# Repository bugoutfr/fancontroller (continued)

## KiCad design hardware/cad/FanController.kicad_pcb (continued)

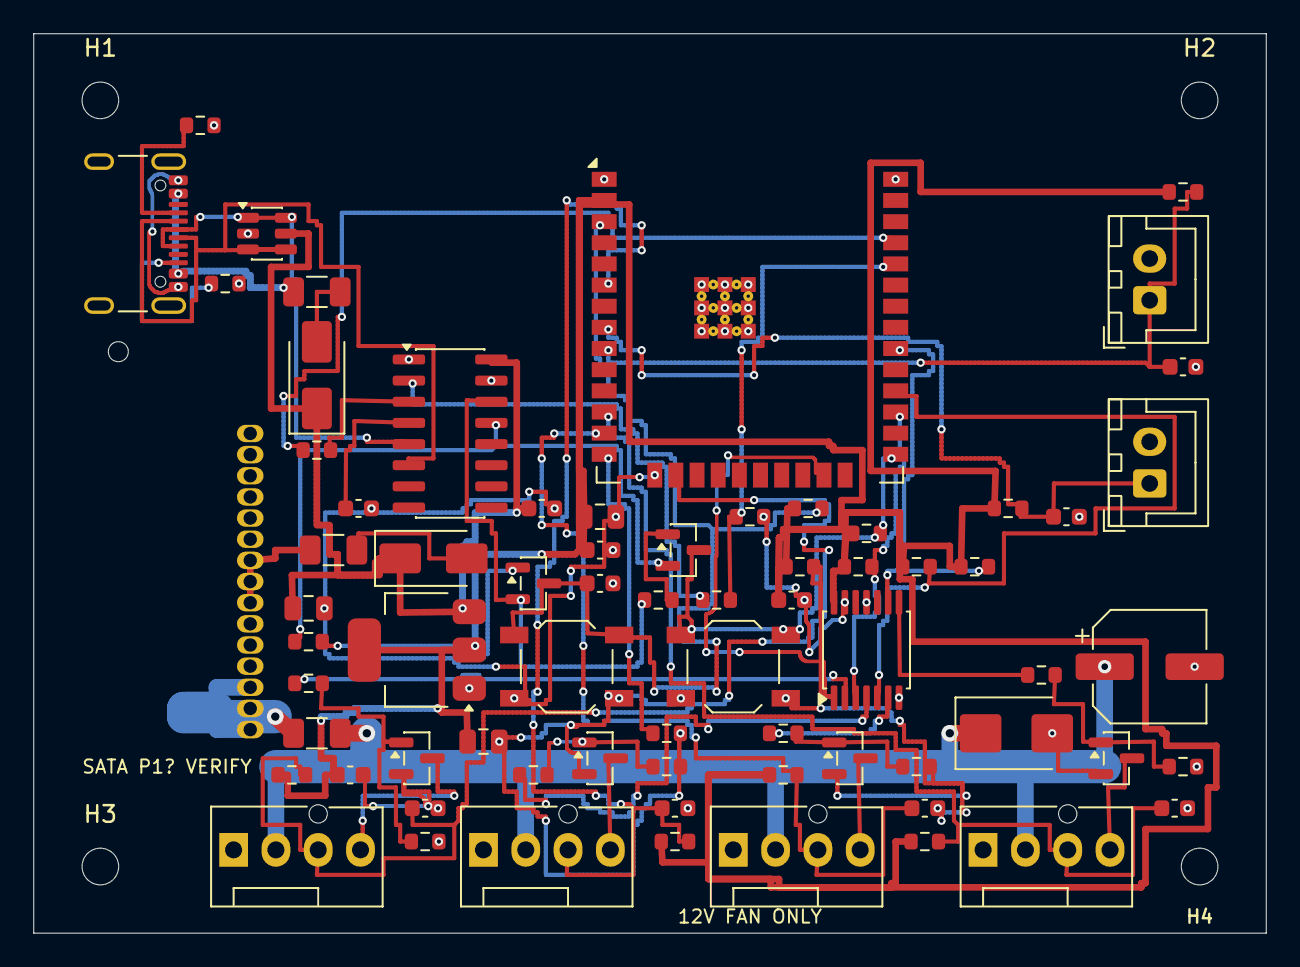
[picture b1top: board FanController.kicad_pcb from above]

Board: 2 copper layers, 74.0 x 54.0 mm, 75 parts (0 on the bottom side), 47 nets.

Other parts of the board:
H1, H2, H3, H4: M2_NPTH_2.2mm; MountingHole_2.2mm_M2

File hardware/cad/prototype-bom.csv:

ref,value,footprint,source
J1,SATA_POWER_B_PROVISIONAL,FanController:SATA_Power_B_Provisional,https://ae-pic-a1.aliexpress-media.com/kf/S0ac0b9d23cc148d9b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
J2,GCT_USB4105-GF-A,Connector_USB:USB_C_Receptacle_GCT_USB4105-xx-A_16P_TopMnt_Horizontal,https://gct.co/files/drawings/usb4105.pdf
F1,3.15A_T_1206_VERIFY_I2T,Fuse:Fuse_1206_3216Metric,
F2,1A_PTC_1206,Fuse:Fuse_1206_3216Metric,
F3,0.5A_PTC_1206,Fuse:Fuse_1206_3216Metric,
D1,SS14,Diode_SMD:D_SMA,https://www.vishay.com/docs/88746/ss12.pdf
D2,SS14,Diode_SMD:D_SMA,https://www.vishay.com/docs/88746/ss12.pdf
D3,SMBJ15A_TVS,Diode_SMD:D_SMB,https://www.vishay.com/docs/88392/smbj.pdf
U2,TLV1117LV33DCYR,Package_TO_SOT_SMD:SOT-223-3_TabPin2,https://www.ti.com/lit/ds/symlink/tlv1117lv.pdf
C1,100uF_25V,Capacitor_SMD:CP_Elec_6.3x7.7,
C2,10uF_10V_X7R,Capacitor_SMD:C_0805_2012Metric,
C3,22uF_6.3V_X5R,Capacitor_SMD:C_0805_2012Metric,
C4,100nF_16V,Capacitor_SMD:C_0603_1608Metric,
C5,100nF_16V,Capacitor_SMD:C_0603_1608Metric,
C6,100nF_16V,Capacitor_SMD:C_0603_1608Metric,
U3,CH340C,Package_SO:SOIC-16_3.9x9.9mm_P1.27mm,https://www.wch-ic.com/downloads/CH340DS1_PDF.html
U4,USBLC6-2SC6,Package_TO_SOT_SMD:SOT-23-6,https://www.st.com/resource/en/datasheet/usblc6-2.pdf
R1,5.1k_1%,Resistor_SMD:R_0603_1608Metric,
R2,5.1k_1%,Resistor_SMD:R_0603_1608Metric,
R3,1k_1%,Resistor_SMD:R_0603_1608Metric,
R4,2k_1%,Resistor_SMD:R_0603_1608Metric,
R5,1k,Resistor_SMD:R_0603_1608Metric,
U1,ESP32-WROOM-32E-N4,RF_Module:ESP32-WROOM-32E,https://documentation.espressif.com/esp32-wroom-32e_esp32-wr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
C7,22uF_6.3V_X5R,Capacitor_SMD:C_0805_2012Metric,
C8,100nF_16V,Capacitor_SMD:C_0603_1608Metric,
R6,10k,Resistor_SMD:R_0603_1608Metric,
C9,1uF_10V_X7R,Capacitor_SMD:C_0603_1608Metric,
R7,10k,Resistor_SMD:R_0603_1608Metric,
R8,10k,Resistor_SMD:R_0603_1608Metric,
SW1,RESET,Button_Switch_SMD:SW_SPST_TL3342,
SW2,BOOT,Button_Switch_SMD:SW_SPST_TL3342,
Q5,MMBT3904LT1G,Package_TO_SOT_SMD:SOT-23,https://www.onsemi.com/pdf/datasheet/mmbt3904lt1-d.pdf
Q6,MMBT3904LT1G,Package_TO_SOT_SMD:SOT-23,https://www.onsemi.com/pdf/datasheet/mmbt3904lt1-d.pdf
R9,10k,Resistor_SMD:R_0603_1608Metric,
R10,10k,Resistor_SMD:R_0603_1608Metric,
U5,SN74LVC14APWR,Package_SO:TSSOP-14_4.4x5mm_P0.65mm,https://www.ti.com/lit/ds/symlink/sn74lvc14a.pdf
C10,100nF_16V,Capacitor_SMD:C_0603_1608Metric,
J3,FAN1_Molex_47053-1000,Connector:FanPinHeader_1x04_P2.54mm_Vertical,https://www.molex.com/en-us/products/part-detail/470531000
Q1,MMBT3904LT1G,Package_TO_SOT_SMD:SOT-23,https://www.onsemi.com/pdf/datasheet/mmbt3904lt1-d.pdf
R11,10k,Resistor_SMD:R_0603_1608Metric,
R15,2.2k,Resistor_SMD:R_0603_1608Metric,
R19,100k,Resistor_SMD:R_0603_1608Metric,
R23,5.23k_1%,Resistor_SMD:R_0603_1608Metric,
C11,100pF_C0G,Capacitor_SMD:C_0603_1608Metric,
J4,FAN2_Molex_47053-1000,Connector:FanPinHeader_1x04_P2.54mm_Vertical,https://www.molex.com/en-us/products/part-detail/470531000
Q2,MMBT3904LT1G,Package_TO_SOT_SMD:SOT-23,https://www.onsemi.com/pdf/datasheet/mmbt3904lt1-d.pdf
R12,10k,Resistor_SMD:R_0603_1608Metric,
R16,2.2k,Resistor_SMD:R_0603_1608Metric,
R20,100k,Resistor_SMD:R_0603_1608Metric,
R24,5.23k_1%,Resistor_SMD:R_0603_1608Metric,
C12,100pF_C0G,Capacitor_SMD:C_0603_1608Metric,
J5,FAN3_Molex_47053-1000,Connector:FanPinHeader_1x04_P2.54mm_Vertical,https://www.molex.com/en-us/products/part-detail/470531000
Q3,MMBT3904LT1G,Package_TO_SOT_SMD:SOT-23,https://www.onsemi.com/pdf/datasheet/mmbt3904lt1-d.pdf
R13,10k,Resistor_SMD:R_0603_1608Metric,
R17,2.2k,Resistor_SMD:R_0603_1608Metric,
R21,100k,Resistor_SMD:R_0603_1608Metric,
R25,5.23k_1%,Resistor_SMD:R_0603_1608Metric,
C13,100pF_C0G,Capacitor_SMD:C_0603_1608Metric,
J6,FAN4_Molex_47053-1000,Connector:FanPinHeader_1x04_P2.54mm_Vertical,https://www.molex.com/en-us/products/part-detail/470531000
Q4,MMBT3904LT1G,Package_TO_SOT_SMD:SOT-23,https://www.onsemi.com/pdf/datasheet/mmbt3904lt1-d.pdf
R14,10k,Resistor_SMD:R_0603_1608Metric,
R18,2.2k,Resistor_SMD:R_0603_1608Metric,
R22,100k,Resistor_SMD:R_0603_1608Metric,
R26,5.23k_1%,Resistor_SMD:R_0603_1608Metric,
C14,100pF_C0G,Capacitor_SMD:C_0603_1608Metric,
J7,NTC1_10k_B3950,Connector_JST:JST_XH_B2B-XH-A_1x02_P2.50mm_Vertical,https://www.jst-mfg.com/product/pdf/eng/eXH.pdf
R27,10k_1%,Resistor_SMD:R_0603_1608Metric,
C15,100nF_16V,Capacitor_SMD:C_0603_1608Metric,
J8,NTC2_10k_B3950,Connector_JST:JST_XH_B2B-XH-A_1x02_P2.50mm_Vertical,https://www.jst-mfg.com/product/pdf/eng/eXH.pdf
R28,10k_1%,Resistor_SMD:R_0603_1608Metric,
C16,100nF_16V,Capacitor_SMD:C_0603_1608Metric,

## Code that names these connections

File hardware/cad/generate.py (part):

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    esp_nets = {i: None for i in range(1, 40)}
    esp_nets.update({1: "GND", 2: "+3V3", 3: "ESP_EN", 6: "FAN2_TACH",
                    8: "NTC2_ADC", 9: "NTC1_ADC", 12: "FAN4_TACH", 13: "FAN3_TACH",
                    14: "GPIO12_STRAP", 15: "GND", 16: "FAN1_TACH", 23: "FAN1_GPIO_PWM",
                    25: "ESP_BOOT", 27: "FAN2_GPIO_PWM", 28: "FAN3_GPIO_PWM",
                    30: "FAN4_GPIO_PWM", 34: "ESP_RX0", 35: "ESP_TX0", 38: "GND", 39: "GND"})
    add("U1", "RF_Module:ESP32-WROOM-32E", "ESP32-WROOM-32E-N4",
        "RF_Module:ESP32-WROOM-32E", esp_nets, (43, 14), 0, (451, 61), ESP)
    capacitor("C7", "22uF_6.3V_X5R", "+3V3", (31.5, 15), (501, 30),
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    resistor("R6", "10k", "+3V3", "ESP_EN", (32, 20), (501, 75))
    capacitor("C9", "1uF_10V_X7R", "ESP_EN", (32, 22), (501, 98))
    resistor("R7", "10k", "+3V3", "ESP_BOOT", (43, 30), (553, 30))
    resistor("R8", "10k", "GPIO12_STRAP", "GND", (34, 25), (553, 53))
    add("SW1", "Switch:SW_Push", "RESET", SFP, {1: "ESP_EN", 2: "GND"},
        (32, 38), 0, (451, 116))
    add("SW2", "Switch:SW_Push", "BOOT", SFP, {1: "ESP_BOOT", 2: "GND"},
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    resistor("R10", "10k", "UART_RTS", "BOOT_BASE", (37, 31), (501, 189))
    # Four inversions followed by four collector-open inversions: HIGH = 100%.
    # LVC at 3.3 V avoids AHCT's 4.5 V minimum on diode-ORed 5 V supplies.
    logic_nets = {1: "FAN1_GPIO_PWM", 2: "INV1", 3: "FAN2_GPIO_PWM", 4: "INV2",
                  5: "FAN3_GPIO_PWM", 6: "INV3", 7: "GND", 8: "INV4",
                  9: "FAN4_GPIO_PWM", 10: None, 11: "GND", 12: None, 13: "GND", 14: "+3V3"}
    add("U5", "74xx:74HC14", "SN74LVC14APWR", "Package_SO:TSSOP-14_4.4x5mm_P0.65mm",
        logic_nets, (50, 37), 90,
        {1: (38, 183), 2: (143, 183), 3: (248, 183), 4: (353, 183),
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    net_names = sorted({item.GetNetname()
                        for fp in b.GetFootprints() for item in fp.Pads()
                        if item.GetNetCode()})
    priority = {"GPIO12_STRAP": 0, "NTC1_ADC": 1, "USB_VBUS": 2,
                "UART_DTR": 3, "UART_RTS": 4, "FAN4_TACH": 5,
                "INV1": 6, "UART_TX_5V": 7, "USB_D+": 8, "USB_D-": 8}
    net_names = sorted((name for name in net_names
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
